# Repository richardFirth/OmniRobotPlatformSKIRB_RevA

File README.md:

# OmniRobotPlatformSKIRB_RevA  
Documentation of my Omni robot platform.

**work in progress, i am still adding stuff as of Jan 18**

The robot is designed to be modular and is based around a 3D Printed/Laser cut chassis.
This has a motor control board that connects to the battery and switch.
The motor control board has a socket that can accept different boards that are plugged in.

Folders:
**Chassis_Assembly**: Documentation of physical assembly of Omnibot platform

**MotorBoard_Assemly**: Documentation of motor driver Board

**XBeeControl_Module**: Documentation of a board to control the omnibot via sparkfun joystick

Different modules can be attached to the shield for control via different methods.  

**CAD Model:**  https://grabcad.com/library/omni-robot-platform-skirb_reva-1  

**Joystick Code and Case:** https://github.com/richardFirth/WirelessJoystick  

Order PCB's in Model  
**Motor Control Board:** https://oshpark.com/shared_projects/BiVYTwTP  
**XBee plugonboard** https://oshpark.com/shared_projects/E1SlzLHo  
**Xbee Board:** https://oshpark.com/shared_projects/hA4cGipD  
**MotorClip** https://oshpark.com/shared_projects/modA4HzY (Need 4)  
**MotorBackplate** https://oshpark.com/shared_projects/eEKy6Eoc (Need 4, optional)

(you need one of each to build the Robot)

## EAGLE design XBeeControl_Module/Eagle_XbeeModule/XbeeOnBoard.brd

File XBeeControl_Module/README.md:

# XBeeControl_Module

Plug-In Module for control with xbee joystick 
https://github.com/richardFirth/WirelessJoystick

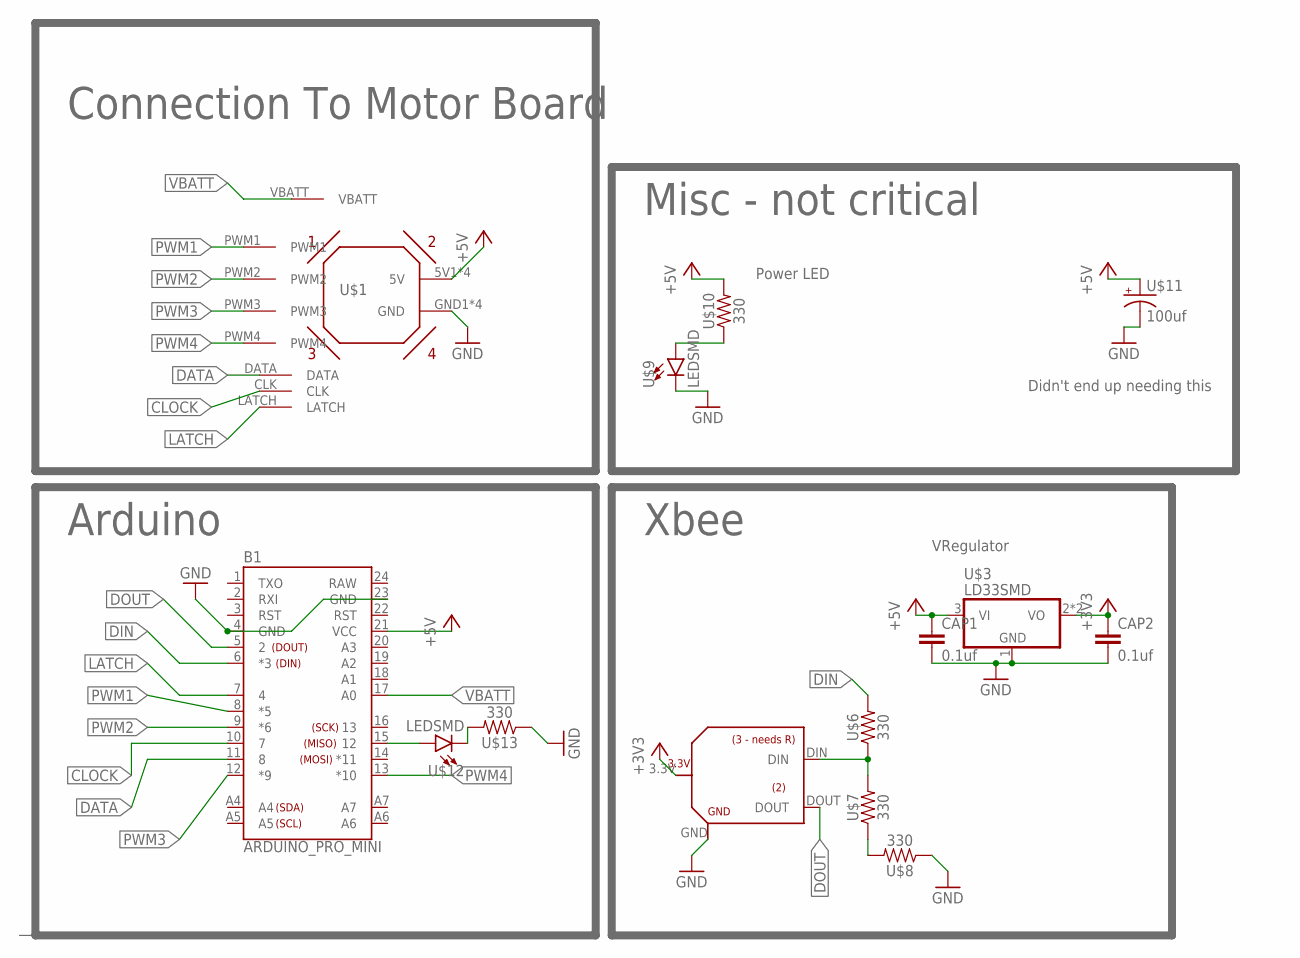
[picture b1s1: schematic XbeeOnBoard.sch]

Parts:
B1: ARDUINO_PRO_MINI
CAP1, CAP2: 0.1uf; C1206
U$1: OMNIBOARD
U$2: XBEE_BOUT
U$3: LD33SMD; SOT223
U$6, U$7, U$8, U$10, U$13: 330; R1206
U$9, U$12: LEDSMD; LED_SMD
U$11: 100uf; CAP_E

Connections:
+3V3: CAP2.1, U$2.3.3V, U$3.2 (VO), U$3.4 (VO)
+5V: B1.21 (VCC), CAP1.1, U$1.5V1 (5V), U$1.5V2 (5V), U$1.5V3 (5V), U$1.5V4 (5V), U$3.3 (VI), U$10.2, U$11.+
CLOCK: B1.10 (7), U$1.CLK
DATA: B1.11 (8), U$1.DATA
DIN: B1.6 (*3), U$6.2
DOUT: B1.5 (2), U$2.DOUT
GND: B1.4 (GND), B1.23 (GND), CAP1.2, CAP2.2, U$1.GND1 (GND), U$1.GND2 (GND), U$1.GND3 (GND), U$1.GND4 (GND), U$2.GND, U$3.1 (GND), U$8.1, U$9.C, U$11.-, U$13.1
LATCH: B1.7 (4), U$1.LATCH
unnamed: U$9.A, U$10.1
unnamed: B1.15 (12), U$12.A
unnamed: U$7.1, U$8.2
unnamed: U$2.DIN, U$6.1, U$7.2
unnamed: U$12.C, U$13.2
PWM1: B1.8 (*5), U$1.PWM1
PWM2: B1.9 (*6), U$1.PWM2
PWM3: B1.12 (*9), U$1.PWM3
PWM4: B1.13 (*10), U$1.PWM4
RAW: B1.24 (RAW)
VBATT: B1.17 (A0), U$1.VBATT

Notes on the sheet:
Arduino
Xbee
VRegulator
Connection To Motor Board
Misc - not critical
Didn't end up needing this
Power LED

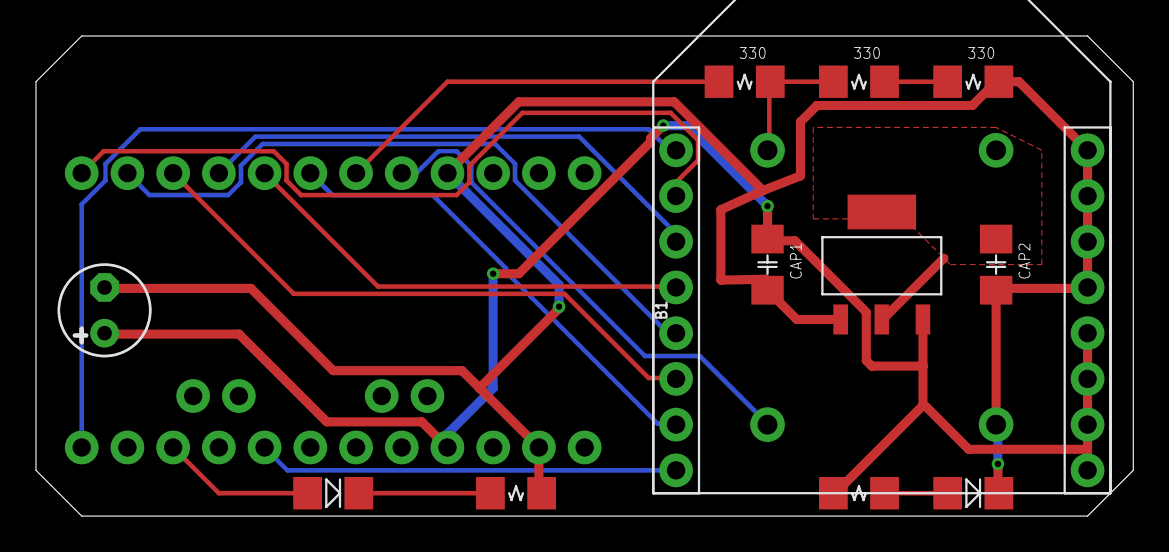
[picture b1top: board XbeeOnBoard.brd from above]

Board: 2 copper layers, 61.0 x 26.7 mm, 14 parts (0 on the bottom side), 18 nets.

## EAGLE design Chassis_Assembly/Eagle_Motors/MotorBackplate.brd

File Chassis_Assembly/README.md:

# Chassis Construction  

instructions for construction of physical chassis.
Uses laser cut & 3D Printed components. 

**CAD Model:**  https://grabcad.com/library/omni-robot-platform-skirb_reva-1

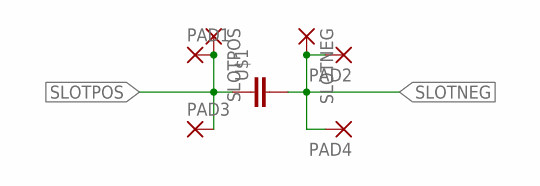
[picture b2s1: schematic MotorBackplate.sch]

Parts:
PAD1, PAD2: PADNRML; PAD_NRML
PAD3, PAD4: PADLG; PAD_LG
SLOTNEG: PAD; SLOTPAD
SLOTPOS: PAD; SLOTPAD
U$1: CAP_SMNORM; CAP_SM

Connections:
SLOTNEG: PAD2.P$2, PAD4.P$2, SLOTNEG.+, U$1.2
SLOTPOS: PAD1.P$2, PAD3.P$2, SLOTPOS.+, U$1.1

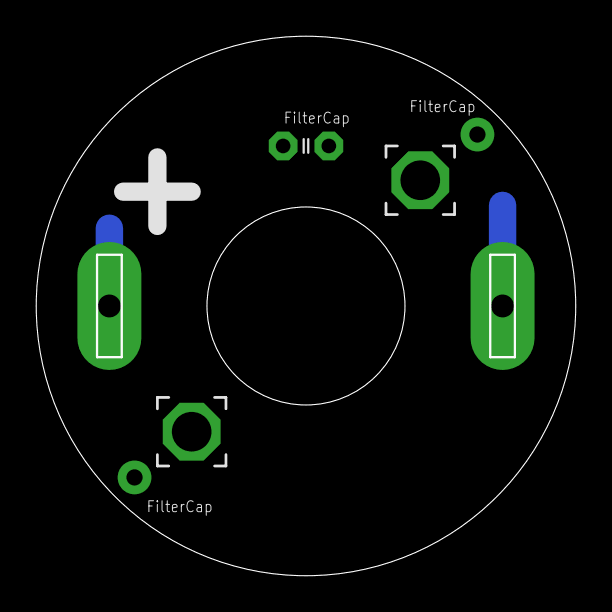
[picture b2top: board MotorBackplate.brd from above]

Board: 2 copper layers, 29.9 x 29.9 mm, 7 parts (0 on the bottom side), 2 nets.

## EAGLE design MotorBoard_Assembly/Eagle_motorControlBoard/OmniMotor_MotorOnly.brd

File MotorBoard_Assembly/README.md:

# Motor Board

Instructions for assembling the motor board.
This is used by each of the modules to control the motors of the omnibot.
It has a common output that can be used by whatever you put above it.

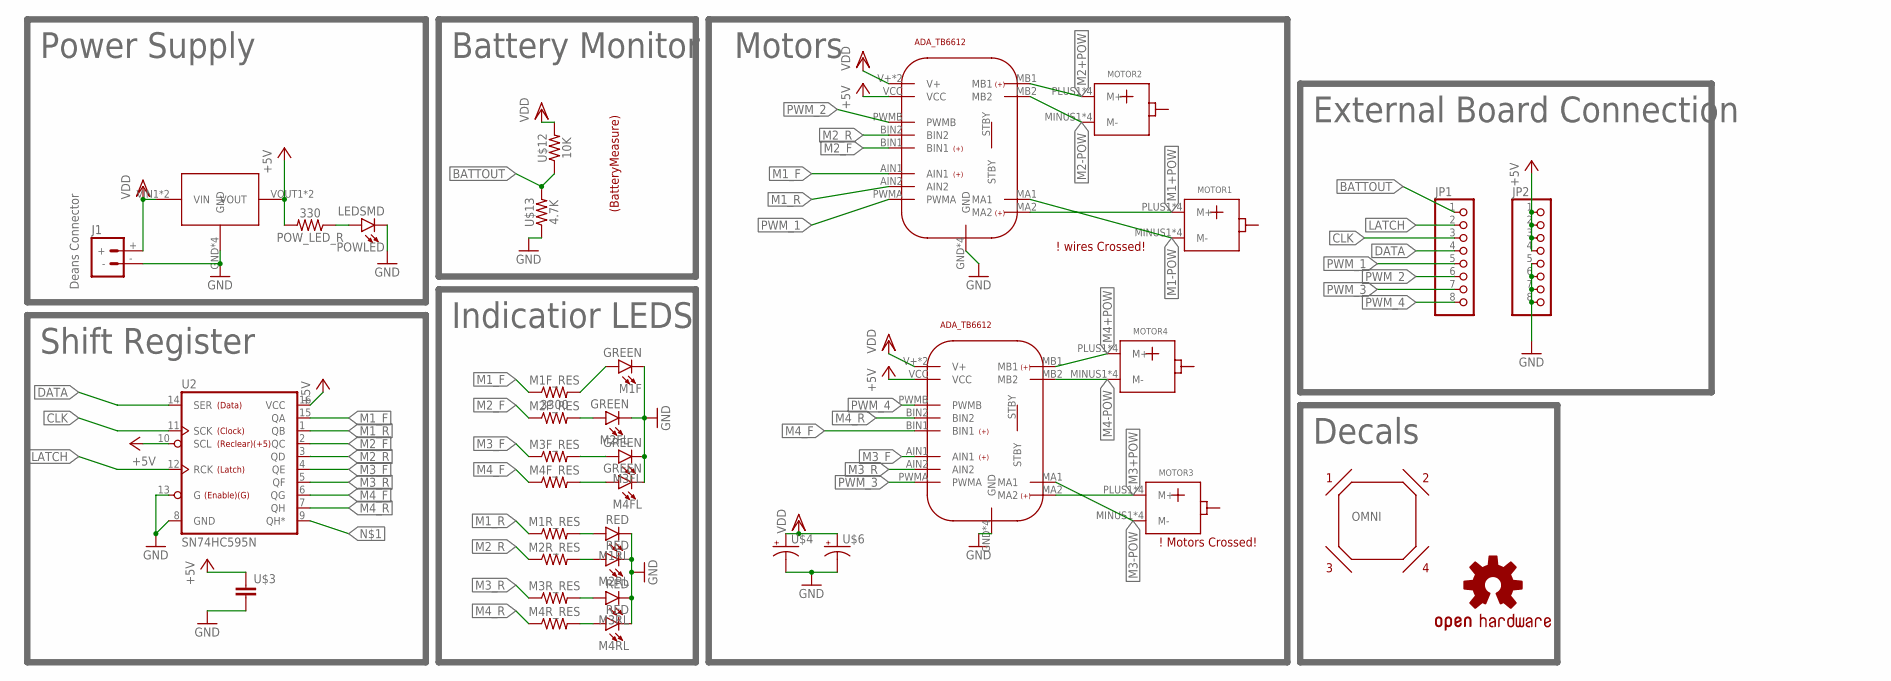
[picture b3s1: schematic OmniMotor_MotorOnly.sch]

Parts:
J1: BATTERY_CONN_DEANS; DEANS
JP1, JP2: PINHD-1X8BIG; 1X08-BIG
LOGO1: OSHW-LOGOL; OSHW-LOGO-L
M1F, M2FL, M3FL, M4FL: GREEN; LED_SMD
M1F_RES: 3300; R1206
M1RL, M2RL, M3RL, M4RL: RED; LED_SMD
M1R_RES, M2F_RES, M2R_RES, M3F_RES, M3R_RES, M4F_RES, M4R_RES: RESISTORSMD; R1206
MOTOR1, MOTOR2, MOTOR3, MOTOR4: MOTOR_DC
OMNI: OMNI
POWLED: LEDSMD; LED_SMD
POW_LED_R: 330; R1206
U2: SN74HC595N; DIP16
U$1, U$2: ADA_TB6612
U$3: CAP_SMCAP; C1206
U$4, U$6: CAP_EMED; CAP_E
U$5: STEPDOWNGREEN; STEPDOWN
U$12: 10K; R1206
U$13: 4.7K; R1206

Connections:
+5V: JP2.1, JP2.2, JP2.3, JP2.4, POW_LED_R.2, U2.10 (SCL), U2.16 (VCC), U$1.VCC, U$2.VCC, U$3.1, U$5.VOUT1 (VOUT), U$5.VOUT2 (VOUT)
BATTOUT: JP1.1, U$12.1, U$13.2
CLK: JP1.3, U2.11 (SCK)
DATA: JP1.4, U2.14 (SER)
GND: J1.-, JP2.5, JP2.6, JP2.7, JP2.8, M1F.C, M1RL.C, M2FL.C, M2RL.C, M3FL.C, M3RL.C, M4FL.C, M4RL.C, POWLED.C, U2.8 (GND), U2.13 (G), U$1.GND, U$1.GND2 (GND), U$1.GND3 (GND), U$1.GND4 (GND), U$2.GND, U$2.GND2 (GND), U$2.GND3 (GND), U$2.GND4 (GND), U$3.2, U$4.-, U$5.GND, U$5.GND2 (GND), U$5.GND3 (GND), U$5.GND4 (GND), U$6.-, U$13.1
LATCH: JP1.2, U2.12 (RCK)
M1+POW: MOTOR1.PLUS1 (M+), MOTOR1.PLUS2 (M+), MOTOR1.PLUS3 (M+), MOTOR1.PLUS4 (M+), U$1.MA2
M1-POW: MOTOR1.MINUS1 (M-), MOTOR1.MINUS2 (M-), MOTOR1.MINUS3 (M-), MOTOR1.MINUS4 (M-), U$1.MA1
M1_F: M1F_RES.1, U2.15 (QA), U$1.AIN1
M1_R: M1R_RES.1, U2.1 (QB), U$1.AIN2
M2+POW: MOTOR2.PLUS1 (M+), MOTOR2.PLUS2 (M+), MOTOR2.PLUS3 (M+), MOTOR2.PLUS4 (M+), U$1.MB1
M2-POW: MOTOR2.MINUS1 (M-), MOTOR2.MINUS2 (M-), MOTOR2.MINUS3 (M-), MOTOR2.MINUS4 (M-), U$1.MB2
M2_F: M2F_RES.1, U2.2 (QC), U$1.BIN1
M2_R: M2R_RES.1, U2.3 (QD), U$1.BIN2
M3+POW: MOTOR3.PLUS1 (M+), MOTOR3.PLUS2 (M+), MOTOR3.PLUS3 (M+), MOTOR3.PLUS4 (M+), U$2.MA2
M3-POW: MOTOR3.MINUS1 (M-), MOTOR3.MINUS2 (M-), MOTOR3.MINUS3 (M-), MOTOR3.MINUS4 (M-), U$2.MA1
M3_F: M3F_RES.1, U2.4 (QE), U$2.AIN1
M3_R: M3R_RES.1, U2.5 (QF), U$2.AIN2
M4+POW: MOTOR4.PLUS1 (M+), MOTOR4.PLUS2 (M+), MOTOR4.PLUS3 (M+), MOTOR4.PLUS4 (M+), U$2.MB1
M4-POW: MOTOR4.MINUS1 (M-), MOTOR4.MINUS2 (M-), MOTOR4.MINUS3 (M-), MOTOR4.MINUS4 (M-), U$2.MB2
M4_F: M4F_RES.1, U2.6 (QG), U$2.BIN1
M4_R: M4R_RES.1, U2.7 (QH), U$2.BIN2
unnamed: POWLED.A, POW_LED_R.1
unnamed: M1F.A, M1F_RES.2
unnamed: M2FL.A, M2F_RES.2
unnamed: M3FL.A, M3F_RES.2
unnamed: M1RL.A, M1R_RES.2
unnamed: M2RL.A, M2R_RES.2
unnamed: M3RL.A, M3R_RES.2
unnamed: M4RL.A, M4R_RES.2
unnamed: M4FL.A, M4F_RES.2
PWM_1: JP1.5, U$1.PWMA
PWM_2: JP1.6, U$1.PWMB
PWM_3: JP1.7, U$2.PWMA
PWM_4: JP1.8, U$2.PWMB
VDD: J1.+, U$1.V+, U$1.V+2 (V+), U$2.V+, U$2.V+2 (V+), U$4.+, U$5.VIN1 (VIN), U$5.VIN2 (VIN), U$6.+, U$12.2

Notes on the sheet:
Shift Register
Motors
! Motors Crossed!
! wires Crossed!
(BatteryMeasure)
Power Supply
Deans Connector
Indicatior LEDS
Battery Monitor
Decals
External Board Connection

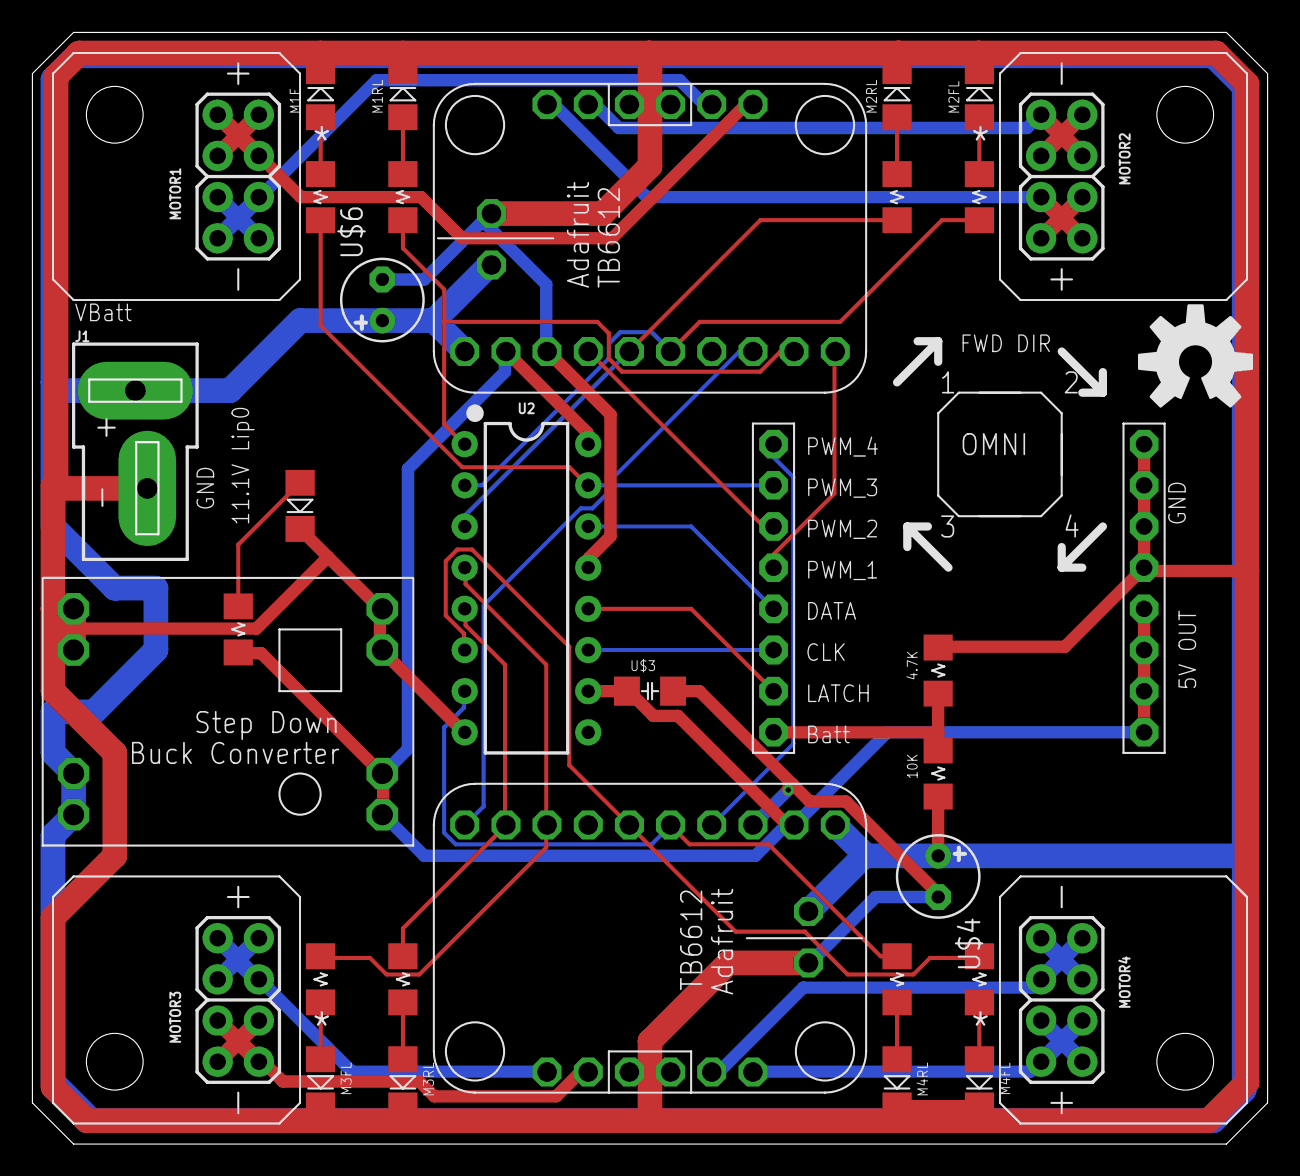
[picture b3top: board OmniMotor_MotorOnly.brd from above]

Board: 2 copper layers, 76.1 x 68.5 mm, 36 parts (0 on the bottom side), 36 nets.

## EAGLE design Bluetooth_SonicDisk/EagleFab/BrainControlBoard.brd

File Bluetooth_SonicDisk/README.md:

# Bluetooth Sonic Disk

This is for a version of the omnibot that uses the sonic disk https://github.com/richardFirth/sonicdisc on top of it to display the surroundings
using bluetooth.

Sonic Disk -> https://github.com/richardFirth/sonicdisc / https://platis.solutions/blog/2017/08/27/sonicdisc-360-ultrasonic-scanner/

Youtube video: https://www.youtube.com/watch?v=5h7yqy7BErE (crappy video - if there is interest I'll make a better one)

**CAD Model:**  https://grabcad.com/library/sonic-disk-mount-1

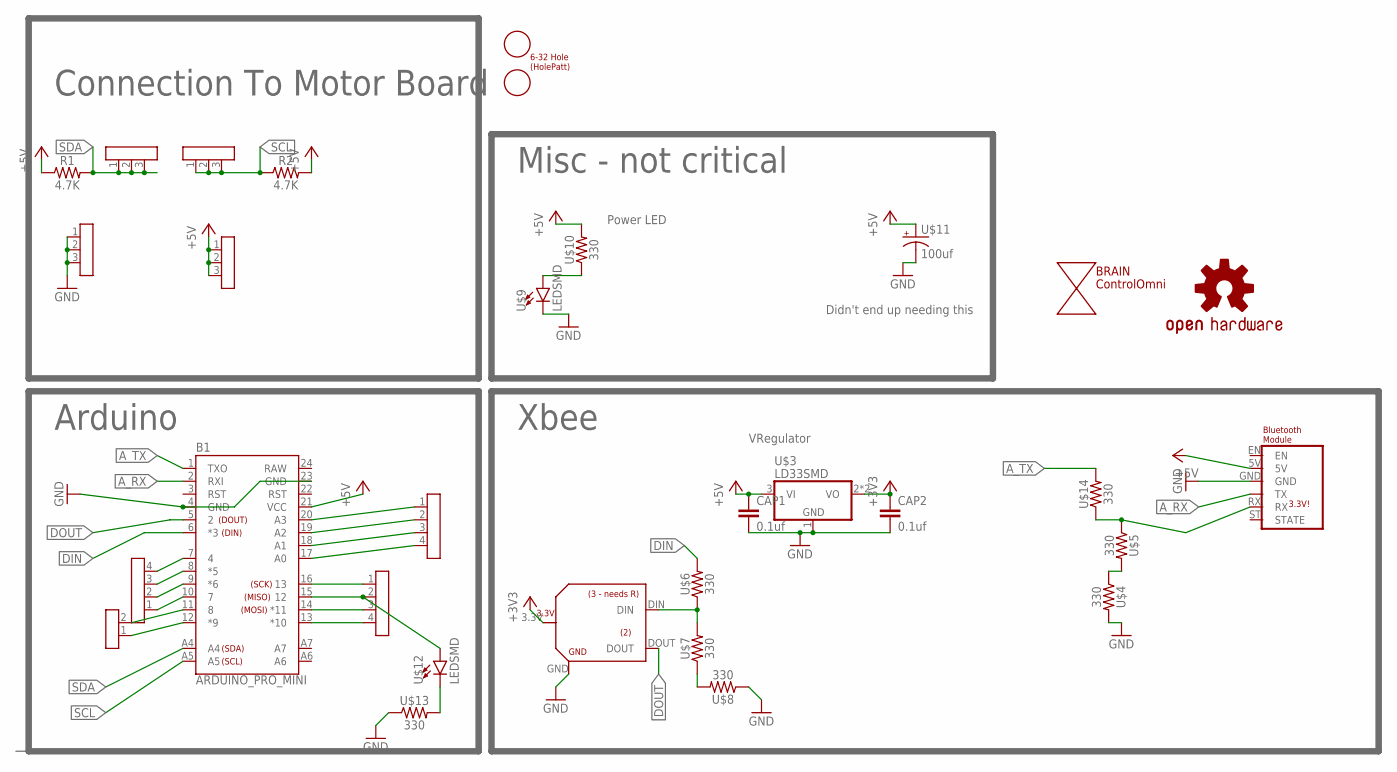
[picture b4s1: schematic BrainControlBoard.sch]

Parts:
B1: ARDUINO_PRO_MINI
BRAIN: ControlOmni; ANNOTATION
CAP1, CAP2: 0.1uf; C1206
LOGO1: OSHW-LOGOM; OSHW-LOGO-M
R1, R2: 4.7K; R1206
U$1: BLUETOOTH
U$2: XBEE_BOUT
U$3: LD33SMD; SOT223
U$4, U$5, U$6, U$7, U$8, U$10, U$13, U$14: 330; R1206
U$9, U$12: LEDSMD; LED_SMD
U$11: 100uf; CAP_E
U$15, U$16, U$17, U$18: 3XHEADER
U$19, U$20, U$22: 4XHEADER
U$21: 2XHEADER
U$23: 632X2

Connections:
+3V3: CAP2.1, U$2.3.3V, U$3.2 (VO), U$3.4 (VO)
+5V: B1.21 (VCC), CAP1.1, R1.1, R2.2, U$1.5V, U$3.3 (VI), U$10.2, U$11.+, U$16.1, U$16.2, U$16.3
A0: B1.17 (A0), U$19.4
A1: B1.18 (A1), U$19.3
A2: B1.19 (A2), U$19.2
A3: B1.20 (A3), U$19.1
A_RX: B1.2 (RXI), U$1.TX
A_TX: B1.1 (TXO), U$14.2
DIN: B1.6 (*3), U$6.2
DOUT: B1.5 (2), U$2.DOUT
GND: B1.4 (GND), B1.23 (GND), CAP1.2, CAP2.2, U$1.GND, U$2.GND, U$3.1 (GND), U$4.2, U$8.1, U$9.C, U$11.-, U$13.1, U$15.1, U$15.2, U$15.3
unnamed: U$9.A, U$10.1
unnamed: U$7.1, U$8.2
unnamed: U$2.DIN, U$6.1, U$7.2
unnamed: U$12.C, U$13.2
unnamed: U$4.1, U$5.2
unnamed: U$1.RX, U$5.1, U$14.1
P4: B1.7 (4), U$20.4
P5: B1.8 (*5), U$20.3
P6: B1.9 (*6), U$20.2
P7: B1.10 (7), U$20.1
P8: B1.11 (8), U$21.2
P9: B1.12 (*9), U$21.1
P10: B1.13 (*10), U$22.4
P11: B1.14 (*11), U$22.3
P12: B1.15 (12), U$12.A, U$22.2
P13: B1.16 (13), U$22.1
RAW: B1.24 (RAW)
SCL: B1.A5, R2.1, U$18.1, U$18.2, U$18.3
SDA: B1.A4, R1.2, U$17.1, U$17.2, U$17.3

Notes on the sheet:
Arduino
Xbee
VRegulator
Connection To Motor Board
Misc - not critical
Didn't end up needing this
Power LED

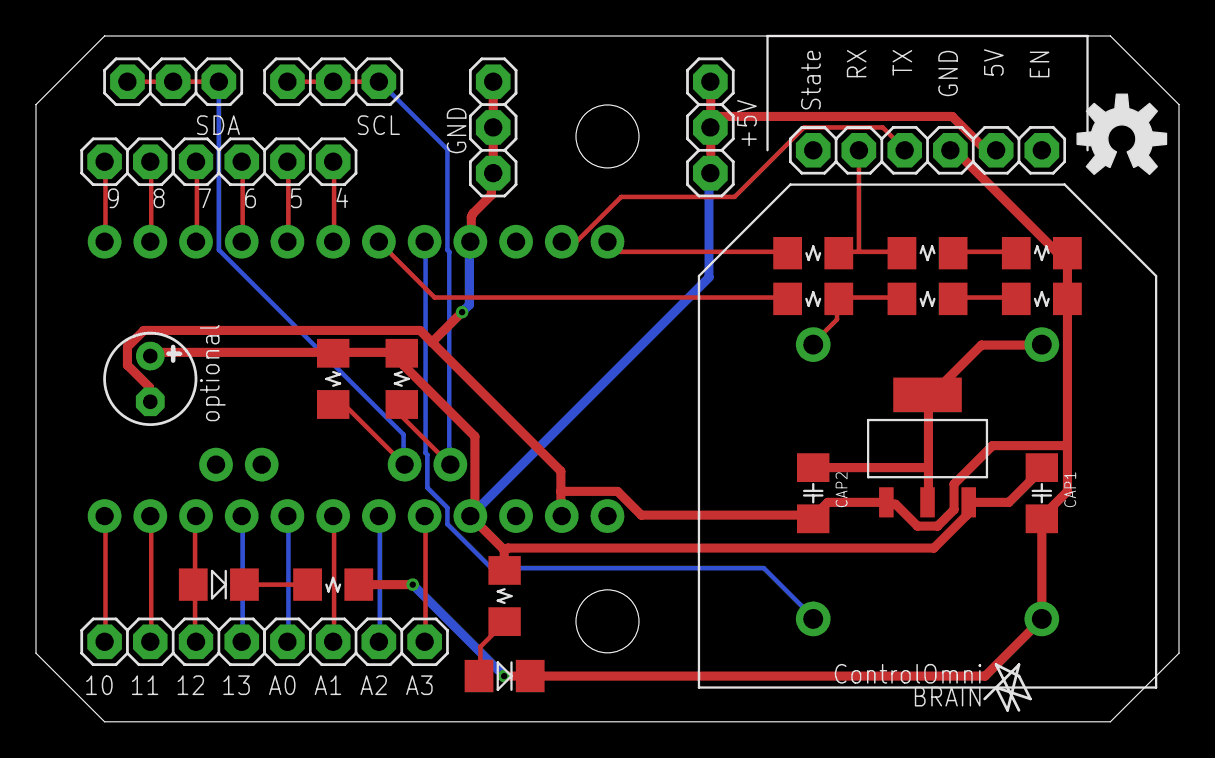
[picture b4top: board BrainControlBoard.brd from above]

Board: 2 copper layers, 63.5 x 38.1 mm, 30 parts (0 on the bottom side), 29 nets.

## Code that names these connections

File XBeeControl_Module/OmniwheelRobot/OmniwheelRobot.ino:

// @@@@@@ #include statements to bring in libraries @@@@@@
   #include <SoftwareSerial.h> // for communicating with the XBee
   #include "OmniRobot.h"
   #include "SerialReceiver.h"
// @@@@@@ #define statements for Pin values @@@@@@
   #define SS_RX 2   //RX Pin For Software Serial
   #define SS_TX 3   //TX Pin For Software Serial
   #define PWM_1 5   //
   #define PWM_2 6   //
   #define PWM_3 9   //
   #define PWM_4 10   //

   #define BlueLED 12   //
   #define BatteryV A0   //
   
#define latchPin 4   //Pin connected to latch pin (ST_CP) of 74HC595
#define clockPin 7   //Pin connected to clock pin (SH_CP) of 74HC595
#define dataPin 8   //Pin connected to Data in (DS) of 74HC595

// for communication with remote. hold incoming values.
SoftwareSerial SSConnection(SS_RX,SS_TX); // RX, TX
SerialReceiver mySerialReceiver(&SSConnection);
OmniRobot OmniBot = OmniRobot(PWM_1,PWM_2,PWM_3,PWM_4,latchPin,clockPin,dataPin,BatteryV);

void setup() {
   Serial.begin(9600);
   Serial.println(F("OmniRobotRobot"));
   Serial.println(F("Last Modified 22Feb2018"));
   mySerialReceiver.startReceiver(9600); // change this to 38400 if using bluetooth
// @@@@@@ set mode of output pins @@@@@@
   pinMode(BlueLED,OUTPUT);   //
   OmniBot.welcomeSequence();
   if (OmniBot.getBatteryVoltage() < 6.0) OmniBot.disableLowVolageAlarm(true); // disable low voltage alarm if we are powering over serial port
}

void loop() 
{
  mySerialReceiver.getLatestData(); // get latest data
  movementLoop(); // move robots
}
 

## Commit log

2018-01-21 update readme by adding eagle links, total replacement of code with new version
2018-01-21 fix typo in Readme
2018-01-26 begin to split project into separate folders
2018-01-26 update folder structrue, add modules
2018-01-26 Add eagle PCB files for Motor Control Board
    Add eagle PCB files for Motor Control Board
2018-01-26 Add eagle PCB files
    Add eagle PCB files for Motor backplate and attachment
2018-01-28 Add DXF files for laser cutting
    these files can be used to laser cut the upper and lower plates. open in mm.
2018-01-28 add 3D Printable STL Files
    STL files for 3D Printing
2018-01-29 add bluetooth module, update readme
2018-02-01 Update README.md
    add link to wireless joystick code
2018-02-01 Create README.md
    add readme
2018-02-01 edit readme
2018-02-01 Add picture
    add picture
2018-02-01 show screenshot
2018-02-01 xbee board
2018-02-01 update xbee board
2018-02-01 add eagle files
    add eagle files
2018-02-04 add eagle PCB
2018-02-05 update PDF instructions, update readme's, rename some code
2018-02-11 update processing3 sketch and OmniRobot object
2018-02-17 update SerialConnector_4
2018-02-23 update to use Serial Reciever Object

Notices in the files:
parts and their libraries:
SparkFun-Aesthetics: Licensing: Creative Commons ShareAlike 4.0 International - https://creativecommons.org/licenses/by-sa/4.0
